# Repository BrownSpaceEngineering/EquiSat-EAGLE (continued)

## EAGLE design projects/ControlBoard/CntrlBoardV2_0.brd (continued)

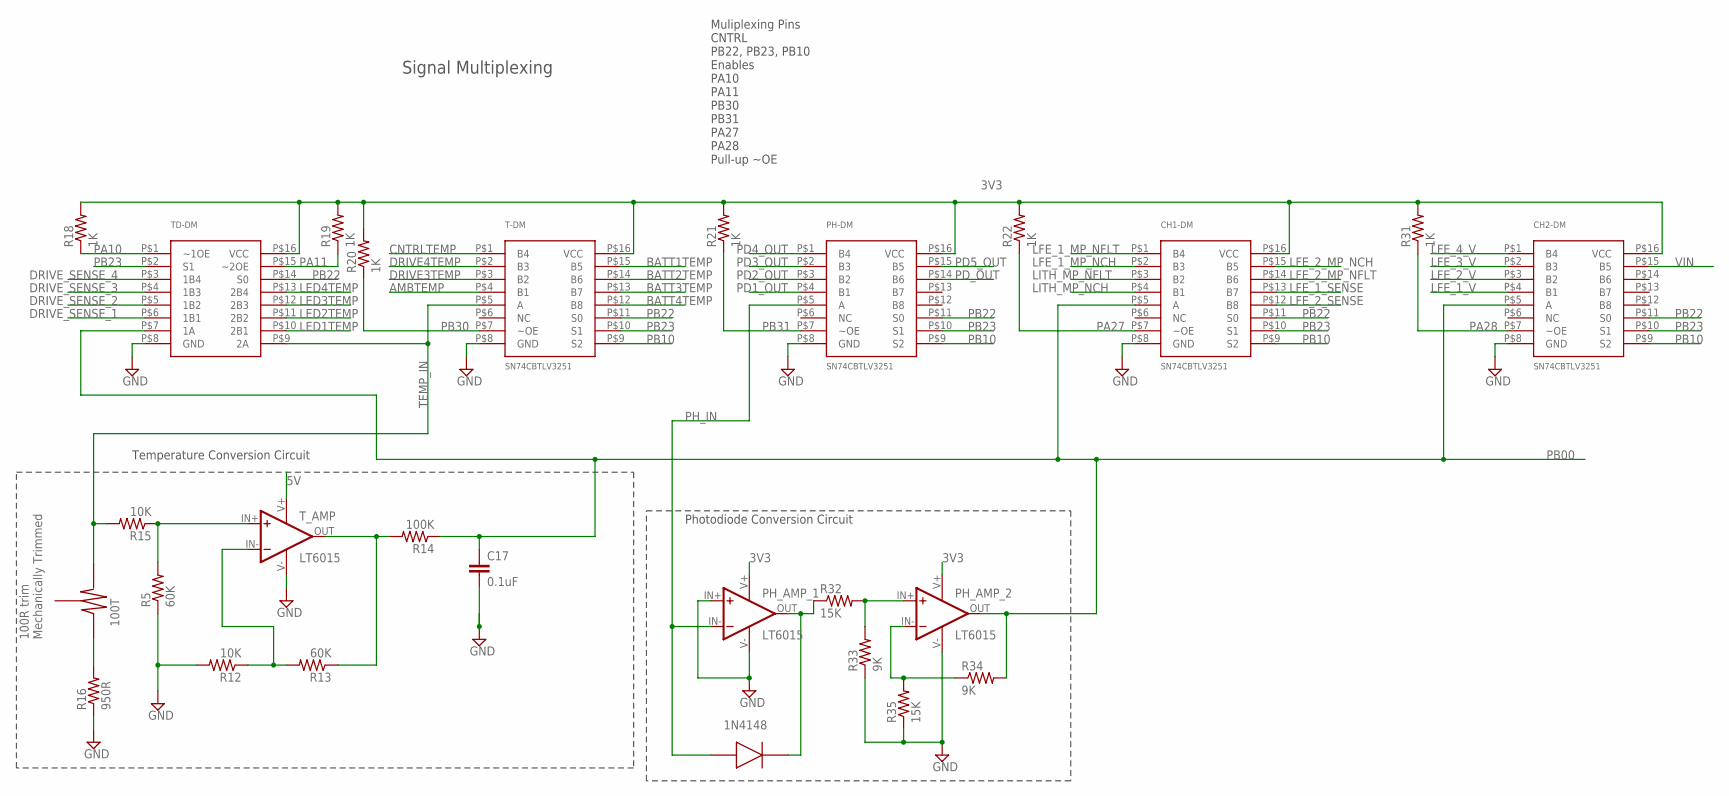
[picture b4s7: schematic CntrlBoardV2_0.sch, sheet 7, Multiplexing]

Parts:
1N4148: 1N4148WS; SOD-323F
100T: TRIMPOT-TC33; TC33X-2
C17: 0.1uF; 0805
CH1-DM, CH2-DM: SN74CBTLV3251; TSSOP-16
PH-DM: SN74CBTLV3251; TSSOP-16
PH_AMP_1, PH_AMP_2: LT6015; SOT23-5
R5, R13: 60K; 0805
R12, R15: 10K; 0805
R14: 100K; 0805
R16: 950R; 0805
R18, R19, R20, R21, R22, R31: 1K; 0805
R32, R35: 15K; 0805
R33, R34: 9K; 0805
T-DM: SN74CBTLV3251; TSSOP-16
TD-DM: SN74CBTLV3253; TSSOP-16
T_AMP: LT6015; SOT23-5

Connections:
3V3: CH1-DM.P$16 (VCC), CH2-DM.P$16 (VCC), PH-DM.P$16 (VCC), PH_AMP_1.V+, PH_AMP_2.V+, R18.2, R19.2, R20.2, R21.2, R22.2, R31.2, T-DM.P$16 (VCC), TD-DM.P$16 (VCC); also elsewhere on the board
5V: T_AMP.V+; also elsewhere on the board
AMBTEMP: T-DM.P$4 (B1); also elsewhere on the board
BATT1TEMP: T-DM.P$15 (B5); also elsewhere on the board
BATT2TEMP: T-DM.P$14 (B6); also elsewhere on the board
BATT3TEMP: T-DM.P$13 (B7); also elsewhere on the board
BATT4TEMP: T-DM.P$12 (B8); also elsewhere on the board
CNTRLTEMP: T-DM.P$1 (B4); also elsewhere on the board
DRIVE3TEMP: T-DM.P$3 (B2); also elsewhere on the board
DRIVE4TEMP: T-DM.P$2 (B3); also elsewhere on the board
DRIVE_SENSE_1: TD-DM.P$6 (1B1); also elsewhere on the board
DRIVE_SENSE_2: TD-DM.P$5 (1B2); also elsewhere on the board
DRIVE_SENSE_3: TD-DM.P$4 (1B3); also elsewhere on the board
DRIVE_SENSE_4: TD-DM.P$3 (1B4); also elsewhere on the board
GND: C17.2, CH1-DM.P$8 (GND), CH2-DM.P$8 (GND), PH-DM.P$8 (GND), PH_AMP_1.IN+, PH_AMP_1.V-, PH_AMP_2.V-, R5.1, R12.2, R16.1, R33.1, R35.1, T-DM.P$8 (GND), TD-DM.P$8 (GND), T_AMP.V-; also elsewhere on the board
LED1TEMP: TD-DM.P$10 (2B1); also elsewhere on the board
LED2TEMP: TD-DM.P$11 (2B2); also elsewhere on the board
LED3TEMP: TD-DM.P$12 (2B3); also elsewhere on the board
LED4TEMP: TD-DM.P$13 (2B4); also elsewhere on the board
LFE_1_MP_NCH: CH1-DM.P$2 (B3); also elsewhere on the board
LFE_1_MP_NFLT: CH1-DM.P$1 (B4); also elsewhere on the board
LFE_1_SENSE: CH1-DM.P$13 (B7); also elsewhere on the board
LFE_1_V: CH2-DM.P$4 (B1); also elsewhere on the board
LFE_2_MP_NCH: CH1-DM.P$15 (B5); also elsewhere on the board
LFE_2_MP_NFLT: CH1-DM.P$14 (B6); also elsewhere on the board
LFE_2_SENSE: CH1-DM.P$12 (B8); also elsewhere on the board
LFE_2_V: CH2-DM.P$3 (B2); also elsewhere on the board
LFE_3_V: CH2-DM.P$2 (B3); also elsewhere on the board
LFE_4_V: CH2-DM.P$1 (B4); also elsewhere on the board
LITH_MP_NCH: CH1-DM.P$4 (B1); also elsewhere on the board
LITH_MP_NFLT: CH1-DM.P$3 (B2); also elsewhere on the board
unnamed: R5.2, R15.1, T_AMP.IN+
unnamed: R13.1, R14.2, T_AMP.OUT
unnamed: R12.1, R13.2, T_AMP.IN-
unnamed: 100T.P$1 (1), R16.2
unnamed: PH_AMP_2.IN+, R32.2, R33.2
unnamed: 1N4148.CATHODE, PH_AMP_1.OUT, R32.1
unnamed: PH_AMP_2.IN-, R34.1, R35.2
PA10: R18.1, TD-DM.P$1 (~1OE); also elsewhere on the board
PA11: R19.1, TD-DM.P$15 (~2OE); also elsewhere on the board
PA27: CH1-DM.P$7 (~OE), R22.1; also elsewhere on the board
PA28: CH2-DM.P$7 (~OE), R31.1; also elsewhere on the board
PB00: C17.1, CH1-DM.P$5 (A), CH2-DM.P$5 (A), PH_AMP_2.OUT, R14.1, R34.2, TD-DM.P$7 (1A); also elsewhere on the board
PB10: CH1-DM.P$9 (S2), CH2-DM.P$9 (S2), PH-DM.P$9 (S2), T-DM.P$9 (S2); also elsewhere on the board
PB22: CH1-DM.P$11 (S0), CH2-DM.P$11 (S0), PH-DM.P$11 (S0), T-DM.P$11 (S0), TD-DM.P$14 (S0); also elsewhere on the board
PB23: CH1-DM.P$10 (S1), CH2-DM.P$10 (S1), PH-DM.P$10 (S1), T-DM.P$10 (S1), TD-DM.P$2 (S1); also elsewhere on the board
PB30: R20.1, T-DM.P$7 (~OE); also elsewhere on the board
PB31: PH-DM.P$7 (~OE), R21.1; also elsewhere on the board
PD1_OUT: PH-DM.P$4 (B1); also elsewhere on the board
PD2_OUT: PH-DM.P$3 (B2); also elsewhere on the board
PD3_OUT: PH-DM.P$2 (B3); also elsewhere on the board
PD4_OUT: PH-DM.P$1 (B4); also elsewhere on the board
PD5_OUT: PH-DM.P$15 (B5); also elsewhere on the board
PD_OUT: PH-DM.P$14 (B6); also elsewhere on the board
PH_IN: 1N4148.ANODE, PH-DM.P$5 (A), PH_AMP_1.IN-
TEMP_IN: 100T.P$3 (3), R15.2, T-DM.P$5 (A), TD-DM.P$9 (2A)
VIN: CH2-DM.P$15 (B5); also elsewhere on the board

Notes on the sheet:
Temperature Conversion Circuit
100R trim Mechanically Trimmed
Muliplexing Pins CNTRL PB22, PB23, PB10 Enables PA10 PA11 PB30 PB31 PA27 PA28 Pull-up ~OE
Photodiode Conversion Circuit
Signal Multiplexing

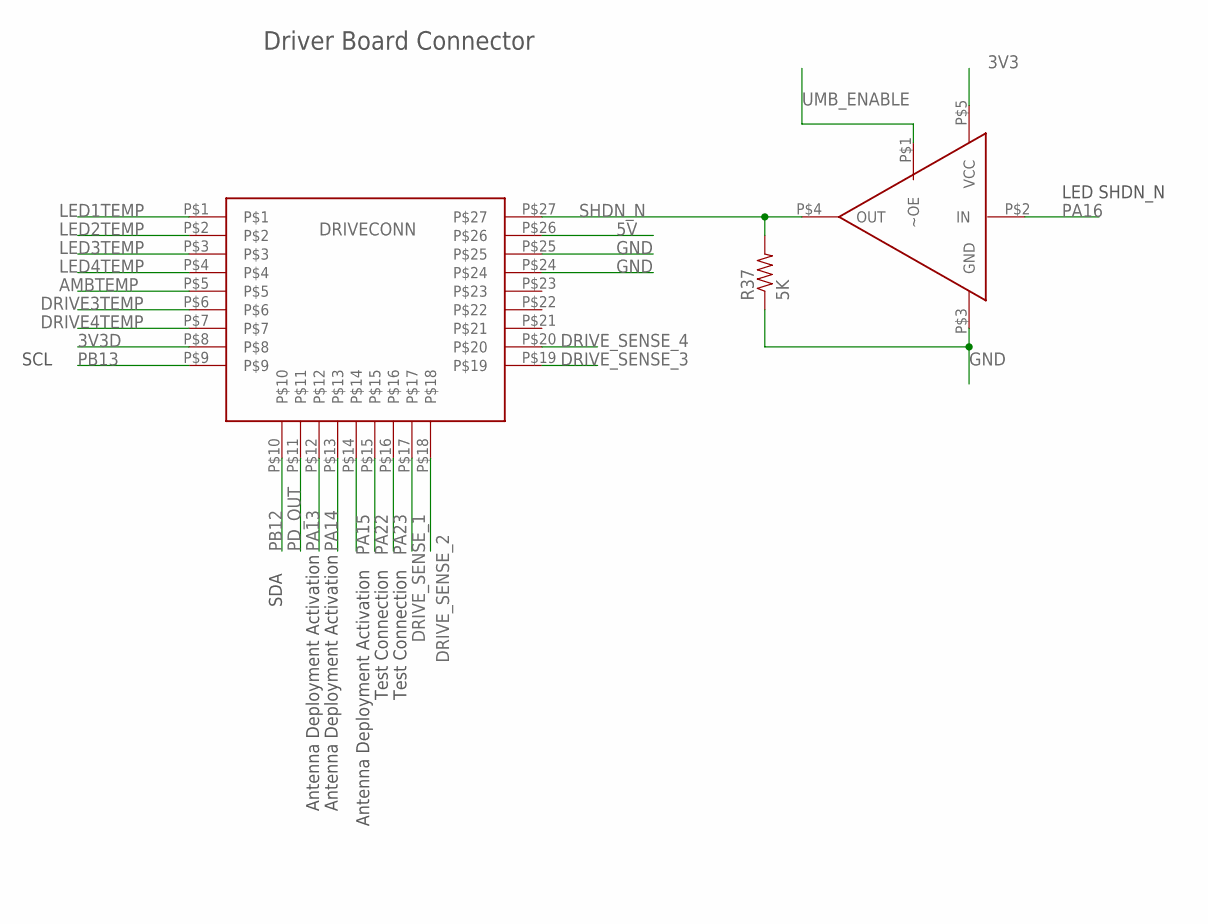
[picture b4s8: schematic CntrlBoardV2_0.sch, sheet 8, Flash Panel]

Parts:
DRIVECONN: HARWIN_27_HOR; HARWIN_DATAMATE_27_HOR
LED_EN_BUF: SN74LVC1G125; SC70
R37: 5K; 0805

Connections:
3V3: LED_EN_BUF.P$5 (VCC); also elsewhere on the board
3V3D: DRIVECONN.P$8; also elsewhere on the board
5V: DRIVECONN.P$26; also elsewhere on the board
AMBTEMP: DRIVECONN.P$5; also elsewhere on the board
DRIVE3TEMP: DRIVECONN.P$6; also elsewhere on the board
DRIVE4TEMP: DRIVECONN.P$7; also elsewhere on the board
DRIVE_SENSE_1: DRIVECONN.P$17; also elsewhere on the board
DRIVE_SENSE_2: DRIVECONN.P$18; also elsewhere on the board
DRIVE_SENSE_3: DRIVECONN.P$19; also elsewhere on the board
DRIVE_SENSE_4: DRIVECONN.P$20; also elsewhere on the board
GND: DRIVECONN.P$24, DRIVECONN.P$25, LED_EN_BUF.P$3 (GND), R37.1; also elsewhere on the board
LED1TEMP: DRIVECONN.P$1; also elsewhere on the board
LED2TEMP: DRIVECONN.P$2; also elsewhere on the board
LED3TEMP: DRIVECONN.P$3; also elsewhere on the board
LED4TEMP: DRIVECONN.P$4; also elsewhere on the board
PA13: DRIVECONN.P$12; also elsewhere on the board
PA14: DRIVECONN.P$13; also elsewhere on the board
PA15: DRIVECONN.P$14; also elsewhere on the board
PA16: LED_EN_BUF.P$2 (IN); also elsewhere on the board
PA22: DRIVECONN.P$15; also elsewhere on the board
PA23: DRIVECONN.P$16; also elsewhere on the board
PB12: DRIVECONN.P$10; also elsewhere on the board
PB13: DRIVECONN.P$9; also elsewhere on the board
PD_OUT: DRIVECONN.P$11; also elsewhere on the board
SHDN_N: DRIVECONN.P$27, LED_EN_BUF.P$4 (OUT), R37.2; also elsewhere on the board
UMB_ENABLE: LED_EN_BUF.P$1 (~OE); also elsewhere on the board

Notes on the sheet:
SCL
SDA
Antenna Deployment Activation
Test Connection
LED SHDN_N
Driver Board Connector

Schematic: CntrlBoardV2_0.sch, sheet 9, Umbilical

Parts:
R36: 1K; 0805
UMBCONN: HARWIN_16; HARWIN_DATAMATE_16

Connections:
BAL_1_ENABLE: UMBCONN.P$15
BAL_2_EN: UMBCONN.P$16
GND: R36.1; also elsewhere on the board
P29: UMBCONN.P$13; also elsewhere on the board
PA17: UMBCONN.P$6; also elsewhere on the board
PA30: UMBCONN.P$2; also elsewhere on the board
PA31: UMBCONN.P$3; also elsewhere on the board
R2: UMBCONN.P$11; also elsewhere on the board
R3: UMBCONN.P$8; also elsewhere on the board
R4: UMBCONN.P$12; also elsewhere on the board
R12: UMBCONN.P$10; also elsewhere on the board
R14: UMBCONN.P$9; also elsewhere on the board
RESETN: UMBCONN.P$1; also elsewhere on the board
SCL: UMBCONN.P$5
SDA: UMBCONN.P$4
SHDN_N: UMBCONN.P$7; also elsewhere on the board
UMB_ENABLE: R36.2, UMBCONN.P$14; also elsewhere on the board

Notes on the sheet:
Programming
I2C
IR Gate
LED SHDN
Radio
Charging
Umbilical Enable
Umbilical Connector

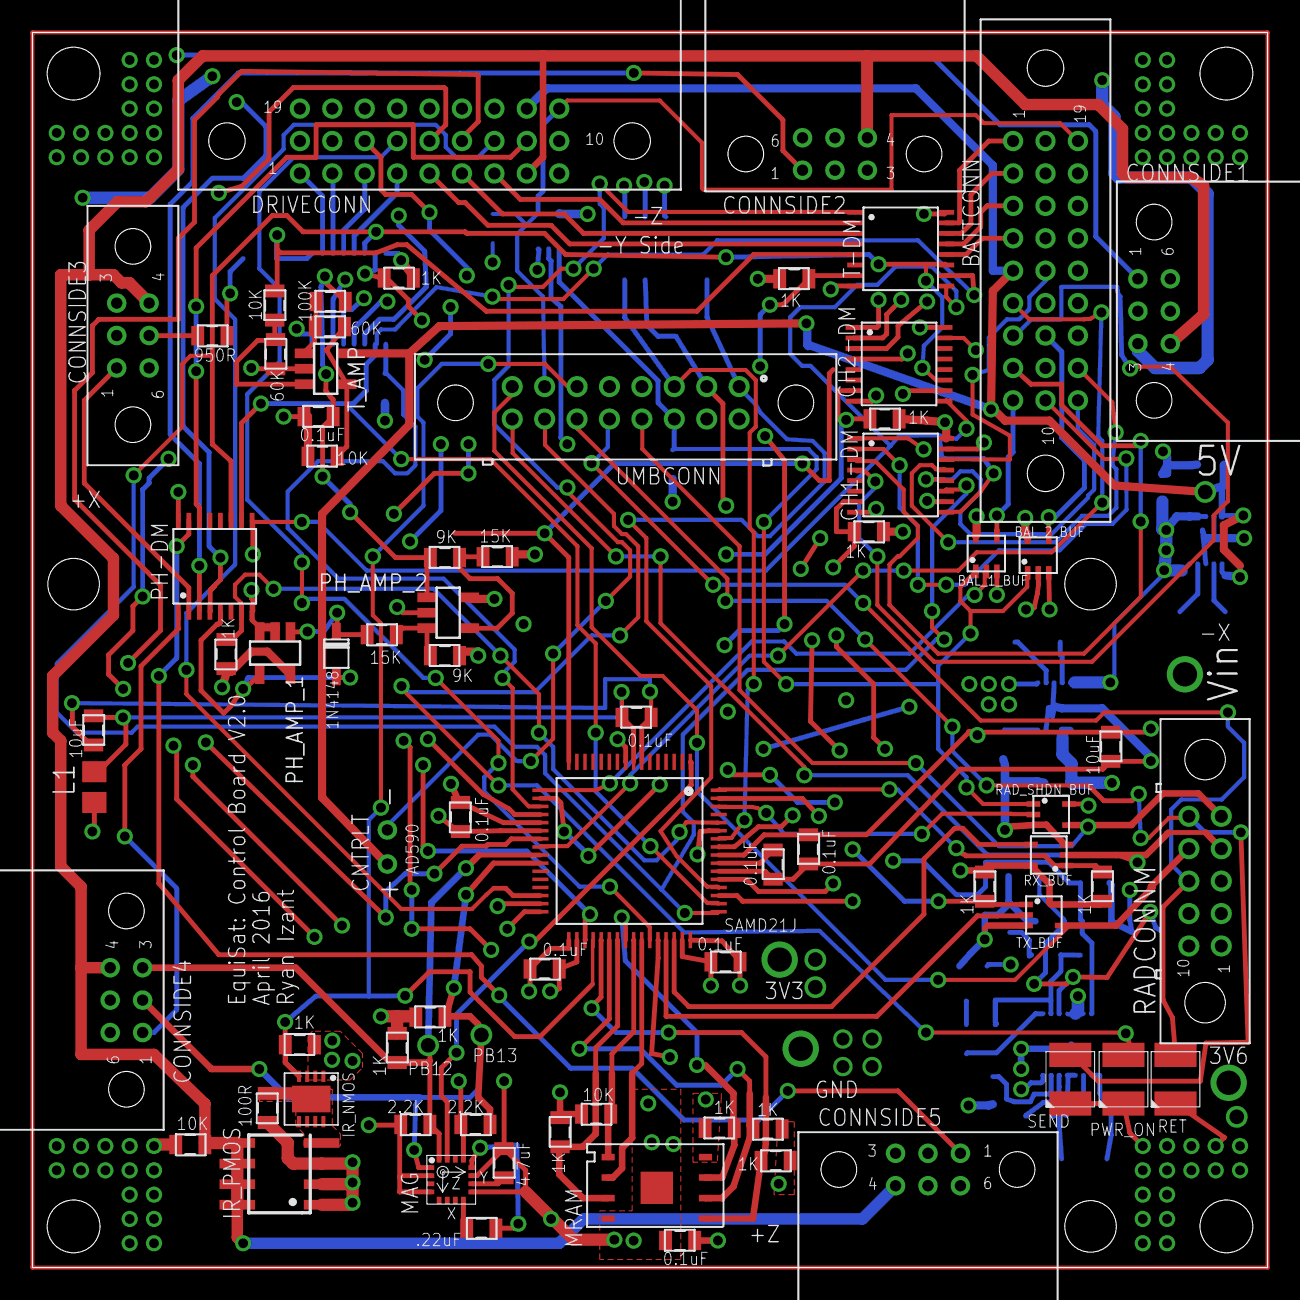
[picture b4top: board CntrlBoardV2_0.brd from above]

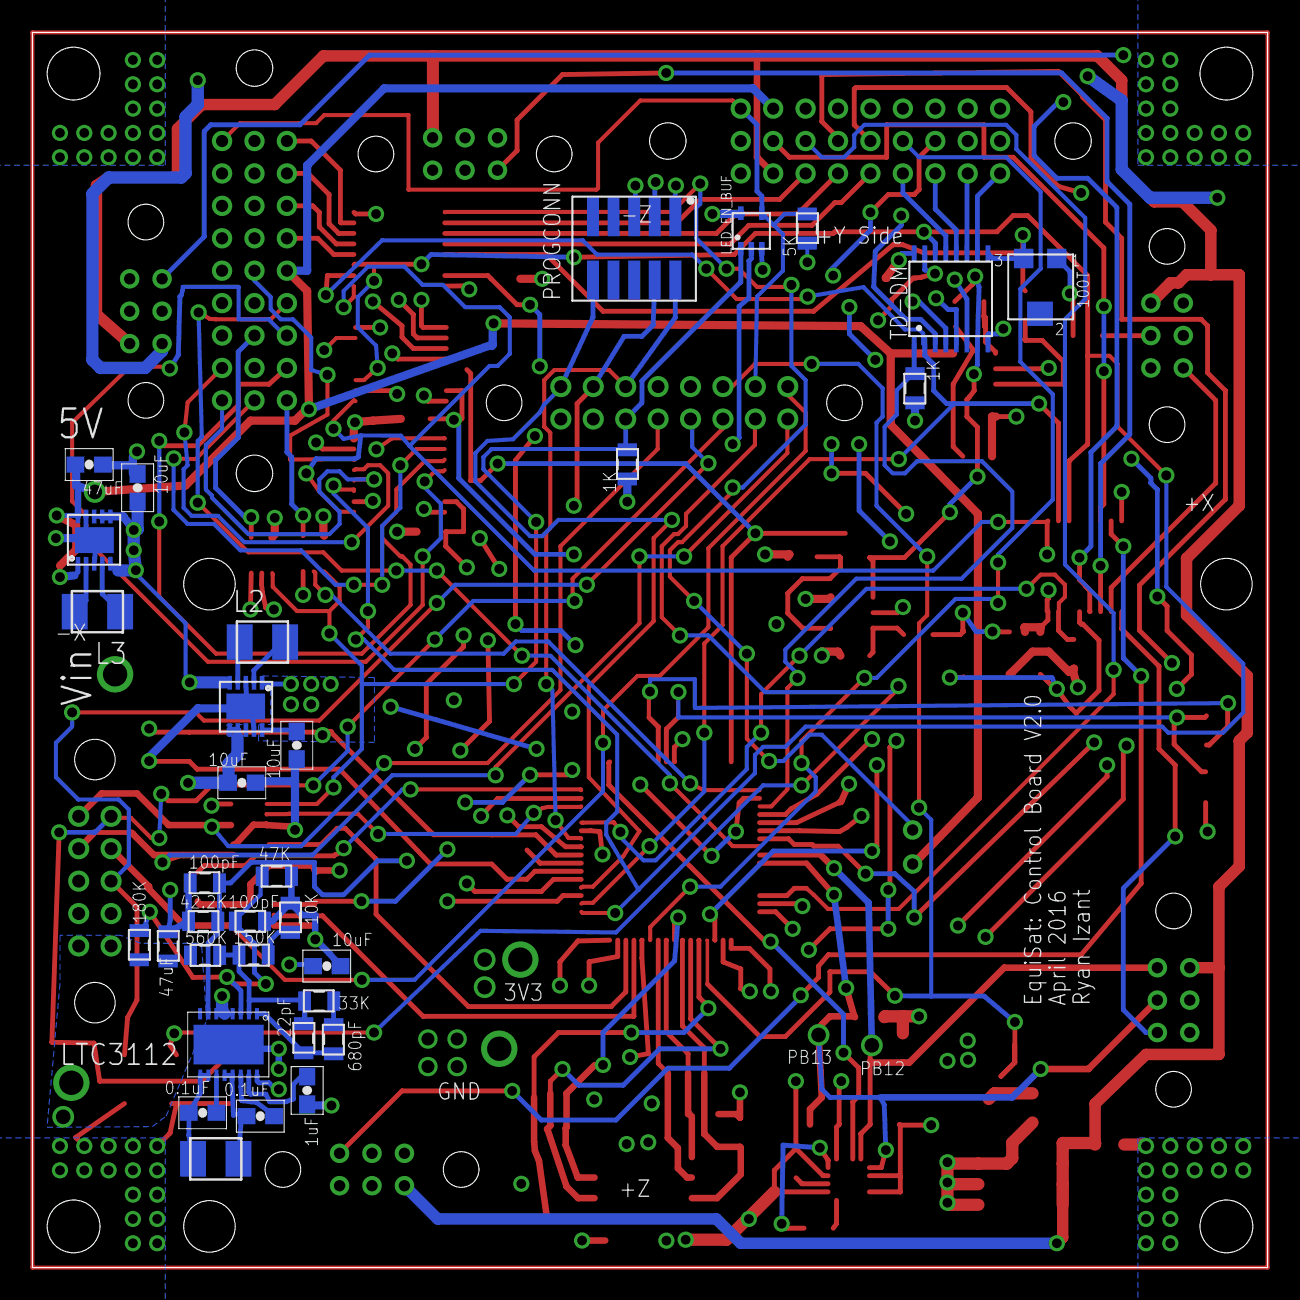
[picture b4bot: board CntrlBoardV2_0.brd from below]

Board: 4 copper layers, 76.2 x 76.2 mm, 106 parts (33 on the bottom side), 117 nets.

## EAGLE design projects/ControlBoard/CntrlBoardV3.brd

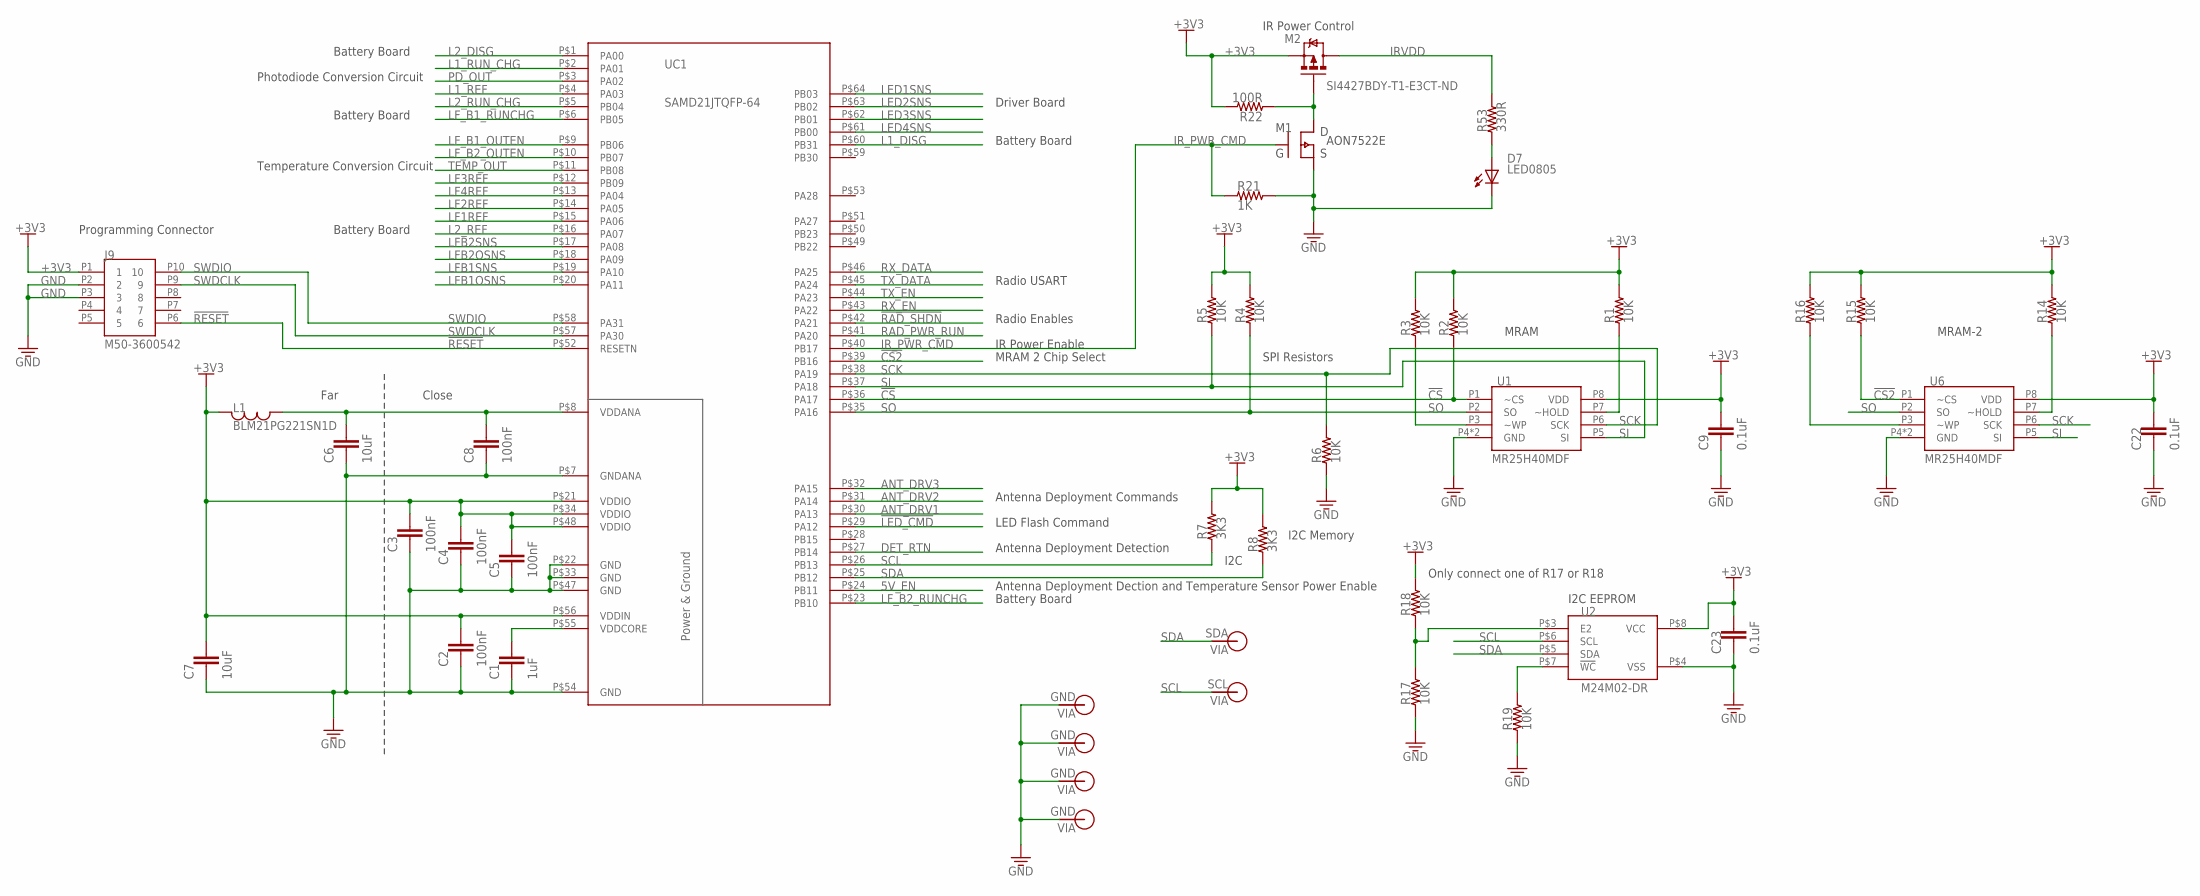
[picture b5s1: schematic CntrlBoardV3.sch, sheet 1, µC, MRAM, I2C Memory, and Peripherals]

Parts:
C1: 1uF; 0805
C2, C3, C4, C5, C8: 100nF; 0805
C6, C7: 10uF; 0805
C9, C22, C23: 0.1uF; 0805
D7: LED0805; 0805-D
J9: M50-3600542; 10PINMALE
L1: BLM21PG221SN1D; 0805
M1: AON7522E; DFN-3X3-8
M2: SI4427BDY-T1-E3CT-ND; SO08
R1, R2, R3, R4, R5, R6, R14, R15, R16, R17, R18, R19: 10K; 0805
R7, R8: 3K3; 0805
R21: 1K; 0805
R22: 100R; 0805
R53: 330R; 0805
U1, U6: MR25H40MDF; 8PXMO-229
U2: M24M02-DR; SO-8
UC1: SAMD21JTQFP-64; TQFP-64
V4: SDA; VIA-60MIL-SQ
V5: SCL; VIA-60MIL-SQ
V9, V10, V11, V12: GND; VIA-60MIL-SQ

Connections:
5V_EN: UC1.P$24 (PB11); also elsewhere on the board
!CS2!: R15.1, U6.P1 (~CS), UC1.P$39 (PB16)
!CS!: R2.1, U1.P1 (~CS), UC1.P$36 (PA17)
!LED_CMD!: UC1.P$29 (PA12); also elsewhere on the board
!RAD_SHDN!: UC1.P$42 (PA21); also elsewhere on the board
!RESET!: J9.P6 (6), UC1.P$52 (RESETN); also elsewhere on the board
+3V3: C2.1, C3.1, C4.1, C5.1, C7.1, C9.1, C22.1, C23.1, J9.P1 (1), L1.1, M2.1 (S), M2.2 (S), M2.3 (S), R1.2, R2.2, R3.2, R4.2, R5.2, R7.2, R8.2, R14.2, R15.2, R16.2, R18.2, R22.2, U1.P8 (VDD), U2.P$8 (VCC), U6.P8 (VDD), UC1.P$21 (VDDIO), UC1.P$34 (VDDIO), UC1.P$48 (VDDIO), UC1.P$56 (VDDIN); also elsewhere on the board
ANT_DRV1: UC1.P$30 (PA13); also elsewhere on the board
ANT_DRV2: UC1.P$31 (PA14); also elsewhere on the board
ANT_DRV3: UC1.P$32 (PA15); also elsewhere on the board
DET_RTN: UC1.P$27 (PB14); also elsewhere on the board
GND: C1.2, C2.2, C3.2, C4.2, C5.2, C6.2, C7.2, C8.2, C9.2, C22.2, C23.2, D7.C, J9.P2 (2), J9.P3 (3), M1.P$1 (S), M1.P$2 (S), M1.P$3 (S), R6.1, R17.1, R19.1, R21.2, U1.P4 (GND), U1.P9 (GND), U2.P$4 (VSS), U6.P4 (GND), U6.P9 (GND), UC1.P$7 (GNDANA), UC1.P$22 (GND), UC1.P$33 (GND), UC1.P$47 (GND), UC1.P$54 (GND), V9.P$1, V10.P$1, V11.P$1, V12.P$1; also elsewhere on the board
IRVDD: M2.5 (D), M2.6 (D), M2.7 (D), M2.8 (D), R53.2; also elsewhere on the board
IR_PWR_CMD: M1.P$4 (G), R21.1, UC1.P$40 (PB17)
L1_DISG: UC1.P$60 (PB31); also elsewhere on the board
L1_REF: UC1.P$4 (PA03); also elsewhere on the board
L1_RUN_CHG: UC1.P$2 (PA01); also elsewhere on the board
L2_DISG: UC1.P$1 (PA00); also elsewhere on the board
L2_REF: UC1.P$16 (PA07); also elsewhere on the board
L2_RUN_CHG: UC1.P$5 (PB04); also elsewhere on the board
LED1SNS: UC1.P$64 (PB03); also elsewhere on the board
LED2SNS: UC1.P$63 (PB02); also elsewhere on the board
LED3SNS: UC1.P$62 (PB01); also elsewhere on the board
LED4SNS: UC1.P$61 (PB00); also elsewhere on the board
LF1REF: UC1.P$15 (PA06); also elsewhere on the board
LF2REF: UC1.P$14 (PA05); also elsewhere on the board
LF3REF: UC1.P$12 (PB09); also elsewhere on the board
LF4REF: UC1.P$13 (PA04); also elsewhere on the board
LFB1OSNS: UC1.P$20 (PA11); also elsewhere on the board
LFB1SNS: UC1.P$19 (PA10); also elsewhere on the board
LFB2OSNS: UC1.P$18 (PA09); also elsewhere on the board
LFB2SNS: UC1.P$17 (PA08); also elsewhere on the board
LF_B1_OUTEN: UC1.P$9 (PB06); also elsewhere on the board
LF_B1_RUNCHG: UC1.P$6 (PB05); also elsewhere on the board
LF_B2_OUTEN: UC1.P$10 (PB07); also elsewhere on the board
LF_B2_RUNCHG: UC1.P$23 (PB10); also elsewhere on the board
unnamed: C6.1, C8.1, L1.2, UC1.P$8 (VDDANA)
unnamed: C1.1, UC1.P$55 (VDDCORE)
unnamed: R3.1, U1.P3 (~WP)
unnamed: R1.1, U1.P7 (~HOLD)
unnamed: R16.1, U6.P3 (~WP)
unnamed: R14.1, U6.P7 (~HOLD)
unnamed: R17.2, R18.1, U2.P$3 (E2)
unnamed: R19.2, U2.P$7 (!WC!)
unnamed: M1.P$5 (D), M1.P$6 (D), M1.P$7 (D), M1.P$8 (D), M1.PAD (D), M2.4 (G), R22.1
unnamed: D7.A, R53.1
PD_OUT: UC1.P$3 (PA02); also elsewhere on the board
RAD_PWR_RUN: UC1.P$41 (PA20); also elsewhere on the board
RX_DATA: UC1.P$46 (PA25); also elsewhere on the board
RX_EN: UC1.P$43 (PA22); also elsewhere on the board
SCK: R6.2, U1.P6 (SCK), U6.P6 (SCK), UC1.P$38 (PA19)
SCL: R7.1, U2.P$6 (SCL), UC1.P$26 (PB13), V5.P$1; also elsewhere on the board
SDA: R8.1, U2.P$5 (SDA), UC1.P$25 (PB12), V4.P$1; also elsewhere on the board
SI: R5.1, U1.P5 (SI), U6.P5 (SI), UC1.P$37 (PA18)
SO: R4.1, U1.P2 (SO), U6.P2 (SO), UC1.P$35 (PA16)
SWDCLK: J9.P9 (9), UC1.P$57 (PA30); also elsewhere on the board
SWDIO: J9.P10 (10), UC1.P$58 (PA31); also elsewhere on the board
TEMP_OUT: UC1.P$11 (PB08); also elsewhere on the board
TX_DATA: UC1.P$45 (PA24); also elsewhere on the board
TX_EN: UC1.P$44 (PA23); also elsewhere on the board

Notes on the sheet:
Close
Far
Programming Connector
MRAM
I2C Memory
I2C
Battery Board
Temperature Conversion Circuit
Photodiode Conversion Circuit
Radio USART
IR Power Enable
Radio Enables
Antenna Deployment Commands
LED Flash Command
Antenna Deployment Detection
Antenna Deployment Dection and Temperature Sensor Power Enable
MRAM-2
MRAM 2 Chip Select
SPI Resistors
Only connect one of R17 or R18
I2C EEPROM
IR Power Control
Driver Board

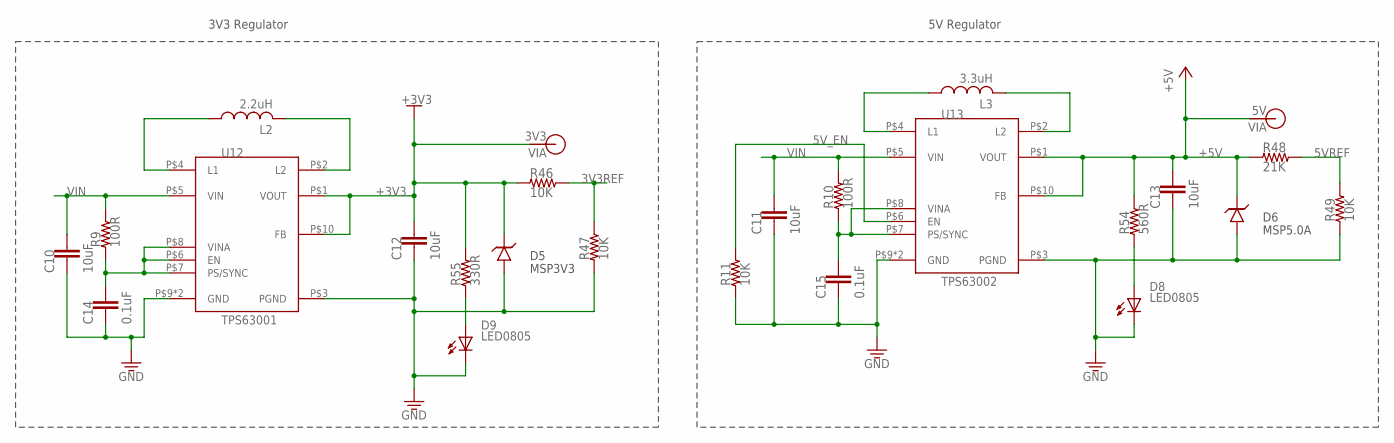
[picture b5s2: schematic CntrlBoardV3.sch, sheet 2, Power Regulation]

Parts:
C10, C11, C12, C13: 10uF; 0805
C14, C15: 0.1uF; 0805
D5: MSP3V3; MICROSMP
D6: MSP5.0A; MICROSMP
D8, D9: LED0805; 0805-D
L2: 2.2uH; L3225M
L3: 3.3uH; L3225M
R9, R10: 100R; 0805
R11, R46, R47, R49: 10K; 0805
R48: 21K; 0805
R54: 560R; 0805
R55: 330R; 0805
U12: TPS63001; QFN10_POWERPAD
U13: TPS63002; QFN10_POWERPAD
V13: 3V3; VIA-60MIL-SQ
V14: 5V; VIA-60MIL-SQ

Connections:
3V3REF: R46.2, R47.2; also elsewhere on the board
5VREF: R48.2, R49.2; also elsewhere on the board
5V_EN: R11.2, U13.P$6 (EN); also elsewhere on the board
+3V3: C12.1, D5.C, R46.1, R55.2, U12.P$1 (VOUT), U12.P$10 (FB), V13.P$1; also elsewhere on the board
+5V: C13.1, D6.C, R48.1, R54.2, U13.P$1 (VOUT), U13.P$10 (FB), V14.P$1; also elsewhere on the board
GND: C10.2, C11.2, C12.2, C13.2, C14.2, C15.2, D5.A, D6.A, D8.C, D9.C, R11.1, R47.1, R49.1, U12.P$3 (PGND), U12.P$9 (GND), U12.PAD (GND), U13.P$3 (PGND), U13.P$9 (GND), U13.PAD (GND); also elsewhere on the board
unnamed: L2.1, U12.P$4 (L1)
unnamed: L2.2, U12.P$2 (L2)
unnamed: L3.1, U13.P$4 (L1)
unnamed: L3.2, U13.P$2 (L2)
unnamed: C14.1, R9.1, U12.P$6 (EN), U12.P$7 (PS/SYNC), U12.P$8 (VINA)
unnamed: C15.1, R10.1, U13.P$7 (PS/SYNC), U13.P$8 (VINA)
unnamed: D8.A, R54.1
unnamed: D9.A, R55.1
VIN: C10.1, C11.1, R9.2, R10.2, U12.P$5 (VIN), U13.P$5 (VIN); also elsewhere on the board

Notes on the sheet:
3V3 Regulator
5V Regulator

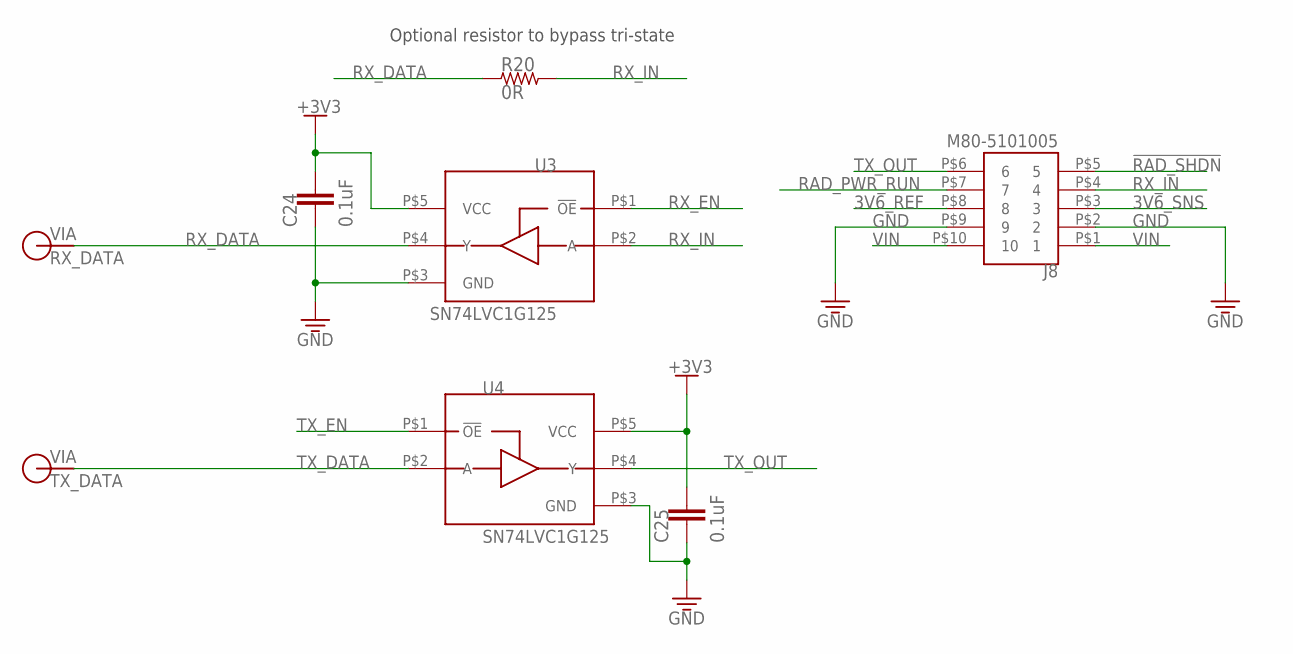
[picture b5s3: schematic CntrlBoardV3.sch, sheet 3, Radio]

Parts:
C24, C25: 0.1uF; 0805
J8: M80-5101005; M80-510
R20: 0R; 0805
U3, U4: SN74LVC1G125; TSOT23-5
V1: RX_DATA; VIA-60MIL-SQ
V2: TX_DATA; VIA-60MIL-SQ

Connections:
3V6_REF: J8.P$8 (8); also elsewhere on the board
3V6_SNS: J8.P$3 (3); also elsewhere on the board
!RAD_SHDN!: J8.P$5 (5); also elsewhere on the board
+3V3: C24.1, C25.1, U3.P$5 (VCC), U4.P$5 (VCC); also elsewhere on the board
GND: C24.2, C25.2, J8.P$2 (2), J8.P$9 (9), U3.P$3 (GND), U4.P$3 (GND); also elsewhere on the board
RAD_PWR_RUN: J8.P$7 (7); also elsewhere on the board
RX_DATA: R20.1, U3.P$4 (Y), V1.P$1; also elsewhere on the board
RX_EN: U3.P$1 (!OE!); also elsewhere on the board
RX_IN: J8.P$4 (4), R20.2, U3.P$2 (A)
TX_DATA: U4.P$2 (A), V2.P$1; also elsewhere on the board
TX_EN: U4.P$1 (!OE!); also elsewhere on the board
TX_OUT: J8.P$6 (6), U4.P$4 (Y)
VIN: J8.P$1 (1), J8.P$10 (10); also elsewhere on the board

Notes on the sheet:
Optional resistor to bypass tri-state

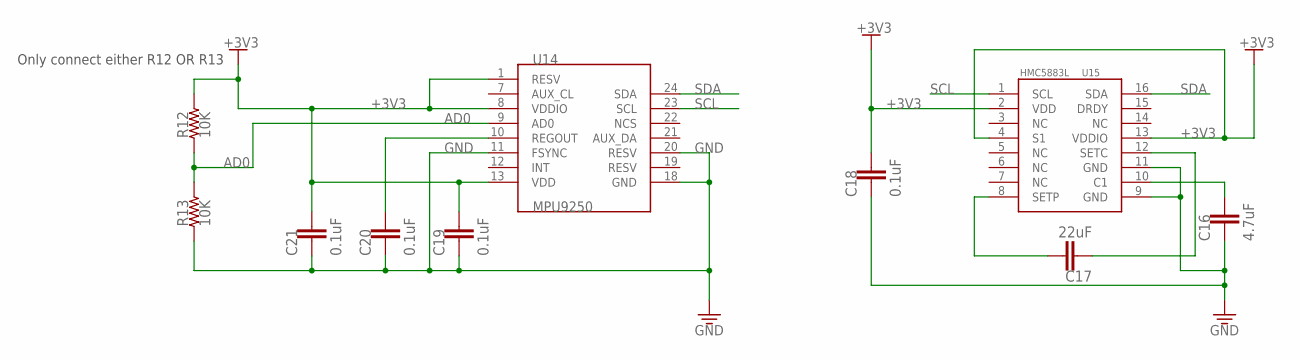
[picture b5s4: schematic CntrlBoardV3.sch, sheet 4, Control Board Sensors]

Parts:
C16: 4.7uF; 0805
C17: 22uF; 0805
C18, C19, C20, C21: 0.1uF; 0805
R12, R13: 10K; 0805
U14: MPU9250; QFN-24-3X3
U15: HMC5883L

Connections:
+3V3: C18.1, C19.1, C21.1, R12.2, U14.1 (RESV), U14.8 (VDDIO), U14.13 (VDD), U15.2 (VDD), U15.4 (S1), U15.13 (VDDIO); also elsewhere on the board
AD0: R12.1, R13.2, U14.9 (AD0)
GND: C16.2, C18.2, C19.2, C20.2, C21.2, R13.1, U14.11 (FSYNC), U14.18 (GND), U14.20 (RESV), U15.9 (GND), U15.11 (GND); also elsewhere on the board
unnamed: C16.1, U15.10 (C1)
unnamed: C20.1, U14.10 (REGOUT)
unnamed: C17.2, U15.12 (SETC)
unnamed: C17.1, U15.8 (SETP)
SCL: U14.23 (SCL), U15.1 (SCL); also elsewhere on the board
SDA: U14.24 (SDA), U15.16 (SDA); also elsewhere on the board

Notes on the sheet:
Only connect either R12 OR R13

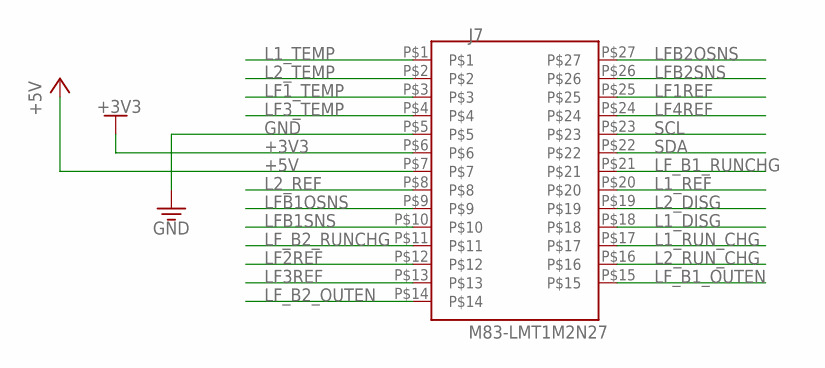
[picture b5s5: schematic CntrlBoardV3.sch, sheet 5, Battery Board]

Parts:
J7: M83-LMT1M2N27

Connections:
+3V3: J7.P$6; also elsewhere on the board
+5V: J7.P$7; also elsewhere on the board
GND: J7.P$5; also elsewhere on the board
L1_DISG: J7.P$18; also elsewhere on the board
L1_REF: J7.P$20; also elsewhere on the board
L1_RUN_CHG: J7.P$17; also elsewhere on the board
L1_TEMP: J7.P$1; also elsewhere on the board
L2_DISG: J7.P$19; also elsewhere on the board
L2_REF: J7.P$8; also elsewhere on the board
L2_RUN_CHG: J7.P$16; also elsewhere on the board
L2_TEMP: J7.P$2; also elsewhere on the board
LF1REF: J7.P$25; also elsewhere on the board
LF1_TEMP: J7.P$3; also elsewhere on the board
LF2REF: J7.P$12; also elsewhere on the board
LF3REF: J7.P$13; also elsewhere on the board
LF3_TEMP: J7.P$4; also elsewhere on the board
LF4REF: J7.P$24; also elsewhere on the board
LFB1OSNS: J7.P$9; also elsewhere on the board
LFB1SNS: J7.P$10; also elsewhere on the board
LFB2OSNS: J7.P$27; also elsewhere on the board
LFB2SNS: J7.P$26; also elsewhere on the board
LF_B1_OUTEN: J7.P$15; also elsewhere on the board
LF_B1_RUNCHG: J7.P$21; also elsewhere on the board
LF_B2_OUTEN: J7.P$14; also elsewhere on the board
LF_B2_RUNCHG: J7.P$11; also elsewhere on the board
SCL: J7.P$23; also elsewhere on the board
SDA: J7.P$22; also elsewhere on the board

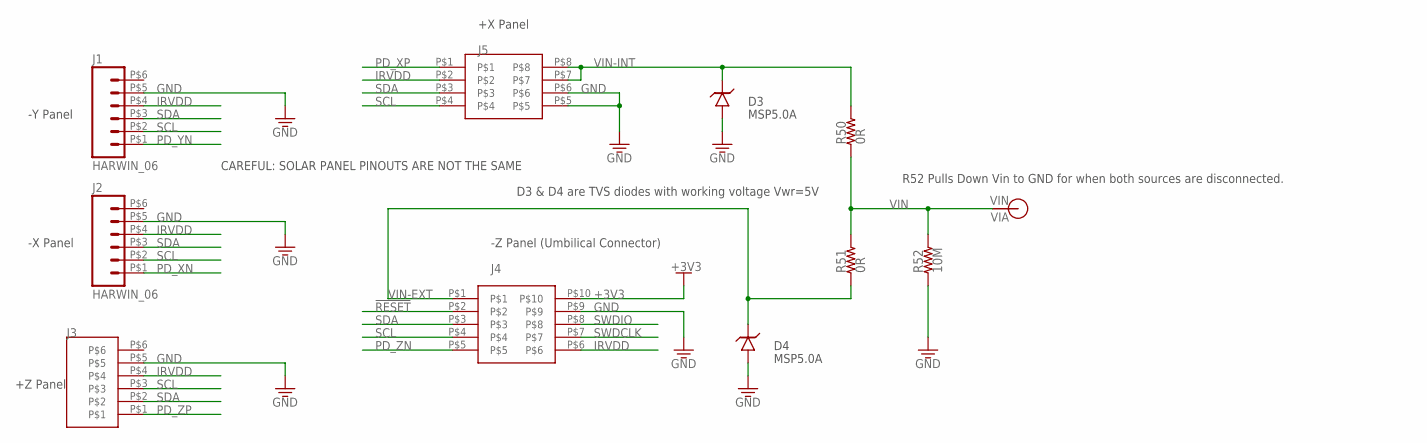
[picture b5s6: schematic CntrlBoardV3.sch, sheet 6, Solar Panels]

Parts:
D3, D4: MSP5.0A; MICROSMP
J1, J2: HARWIN_06; HARWIN_DATAMATE_6
J3: M80-54006
J4: M80-54010
J5: M80-54008
R50, R51: 0R; 1210
R52: 10M; 0805
V3: VIN; VIA-60MIL-SQ

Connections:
!RESET!: J4.P$2; also elsewhere on the board
+3V3: J4.P$10; also elsewhere on the board
GND: D3.A, D4.A, J1.P$5 (5), J2.P$5 (5), J3.P$5, J4.P$9, J5.P$5, J5.P$6, R52.1; also elsewhere on the board
IRVDD: J1.P$4 (4), J2.P$4 (4), J3.P$4, J4.P$6, J5.P$2; also elsewhere on the board
PD_XN: J2.P$1 (1); also elsewhere on the board
PD_XP: J5.P$1; also elsewhere on the board
PD_YN: J1.P$1 (1); also elsewhere on the board
PD_ZN: J4.P$5; also elsewhere on the board
PD_ZP: J3.P$1; also elsewhere on the board
SCL: J1.P$2 (2), J2.P$2 (2), J3.P$3, J4.P$4, J5.P$4; also elsewhere on the board
SDA: J1.P$3 (3), J2.P$3 (3), J3.P$2, J4.P$3, J5.P$3; also elsewhere on the board
SWDCLK: J4.P$7; also elsewhere on the board
SWDIO: J4.P$8; also elsewhere on the board
VIN: R50.P$1 (1), R51.P$2 (2), R52.2, V3.P$1; also elsewhere on the board
VIN-EXT: D4.C, J4.P$1, R51.P$1 (1)
VIN-INT: D3.C, J5.P$7, J5.P$8, R50.P$2 (2)

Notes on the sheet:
-Y Panel
-X Panel
+Z Panel
+X Panel
-Z Panel (Umbilical Connector)
R52 Pulls Down Vin to GND for when both sources are disconnected.
D3 & D4 are TVS diodes with working voltage Vwr=5V
CAREFUL: SOLAR PANEL PINOUTS ARE NOT THE SAME

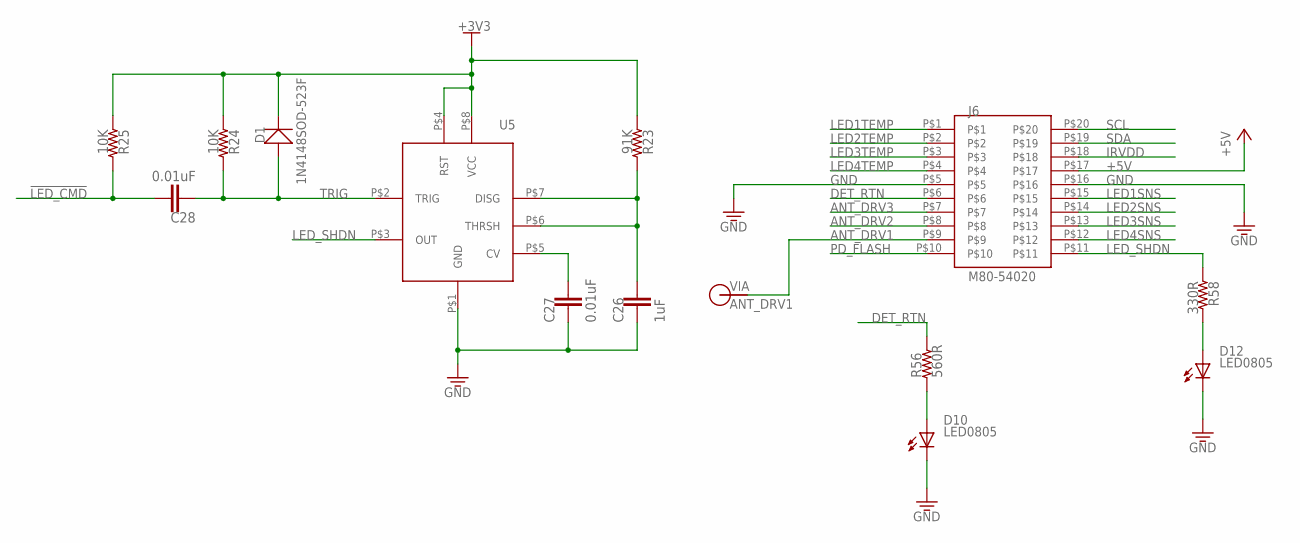
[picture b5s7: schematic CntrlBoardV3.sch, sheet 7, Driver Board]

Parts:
C26: 1uF; 0805
C27, C28: 0.01uF; 0805
D1: 1N4148SOD-523F; SOD-523F
D10, D12: LED0805; 0805-D
J6: M80-54020
R23: 91K; 0805
R24, R25: 10K; 0805
R56: 560R; 0805
R58: 330R; 0805
U5: TLC555; SO-8
V6: ANT_DRV1; VIA-60MIL-SQ

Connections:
!LED_CMD!: C28.1, R25.2; also elsewhere on the board
+3V3: D1.C, R23.1, R24.1, R25.1, U5.P$4 (RST), U5.P$8 (VCC); also elsewhere on the board
+5V: J6.P$17; also elsewhere on the board
ANT_DRV1: J6.P$9, V6.P$1; also elsewhere on the board
ANT_DRV2: J6.P$8; also elsewhere on the board
ANT_DRV3: J6.P$7; also elsewhere on the board
DET_RTN: J6.P$6, R56.2; also elsewhere on the board
GND: C26.2, C27.2, D10.C, D12.C, J6.P$5, J6.P$16, U5.P$1 (GND); also elsewhere on the board
IRVDD: J6.P$18; also elsewhere on the board
LED1SNS: J6.P$15; also elsewhere on the board
LED1TEMP: J6.P$1; also elsewhere on the board
LED2SNS: J6.P$14; also elsewhere on the board
LED2TEMP: J6.P$2; also elsewhere on the board
LED3SNS: J6.P$13; also elsewhere on the board
LED3TEMP: J6.P$3; also elsewhere on the board
LED4SNS: J6.P$12; also elsewhere on the board
LED4TEMP: J6.P$4; also elsewhere on the board
LED_SHDN: J6.P$11, R58.1, U5.P$3 (OUT)
unnamed: C26.1, R23.2, U5.P$6 (THRSH), U5.P$7 (DISG)
unnamed: C27.1, U5.P$5 (CV)
unnamed: D10.A, R56.1
unnamed: D12.A, R58.2
PD_FLASH: J6.P$10; also elsewhere on the board
SCL: J6.P$20; also elsewhere on the board
SDA: J6.P$19; also elsewhere on the board
TRIG: C28.2, D1.A, R24.2, U5.P$2 (TRIG)
